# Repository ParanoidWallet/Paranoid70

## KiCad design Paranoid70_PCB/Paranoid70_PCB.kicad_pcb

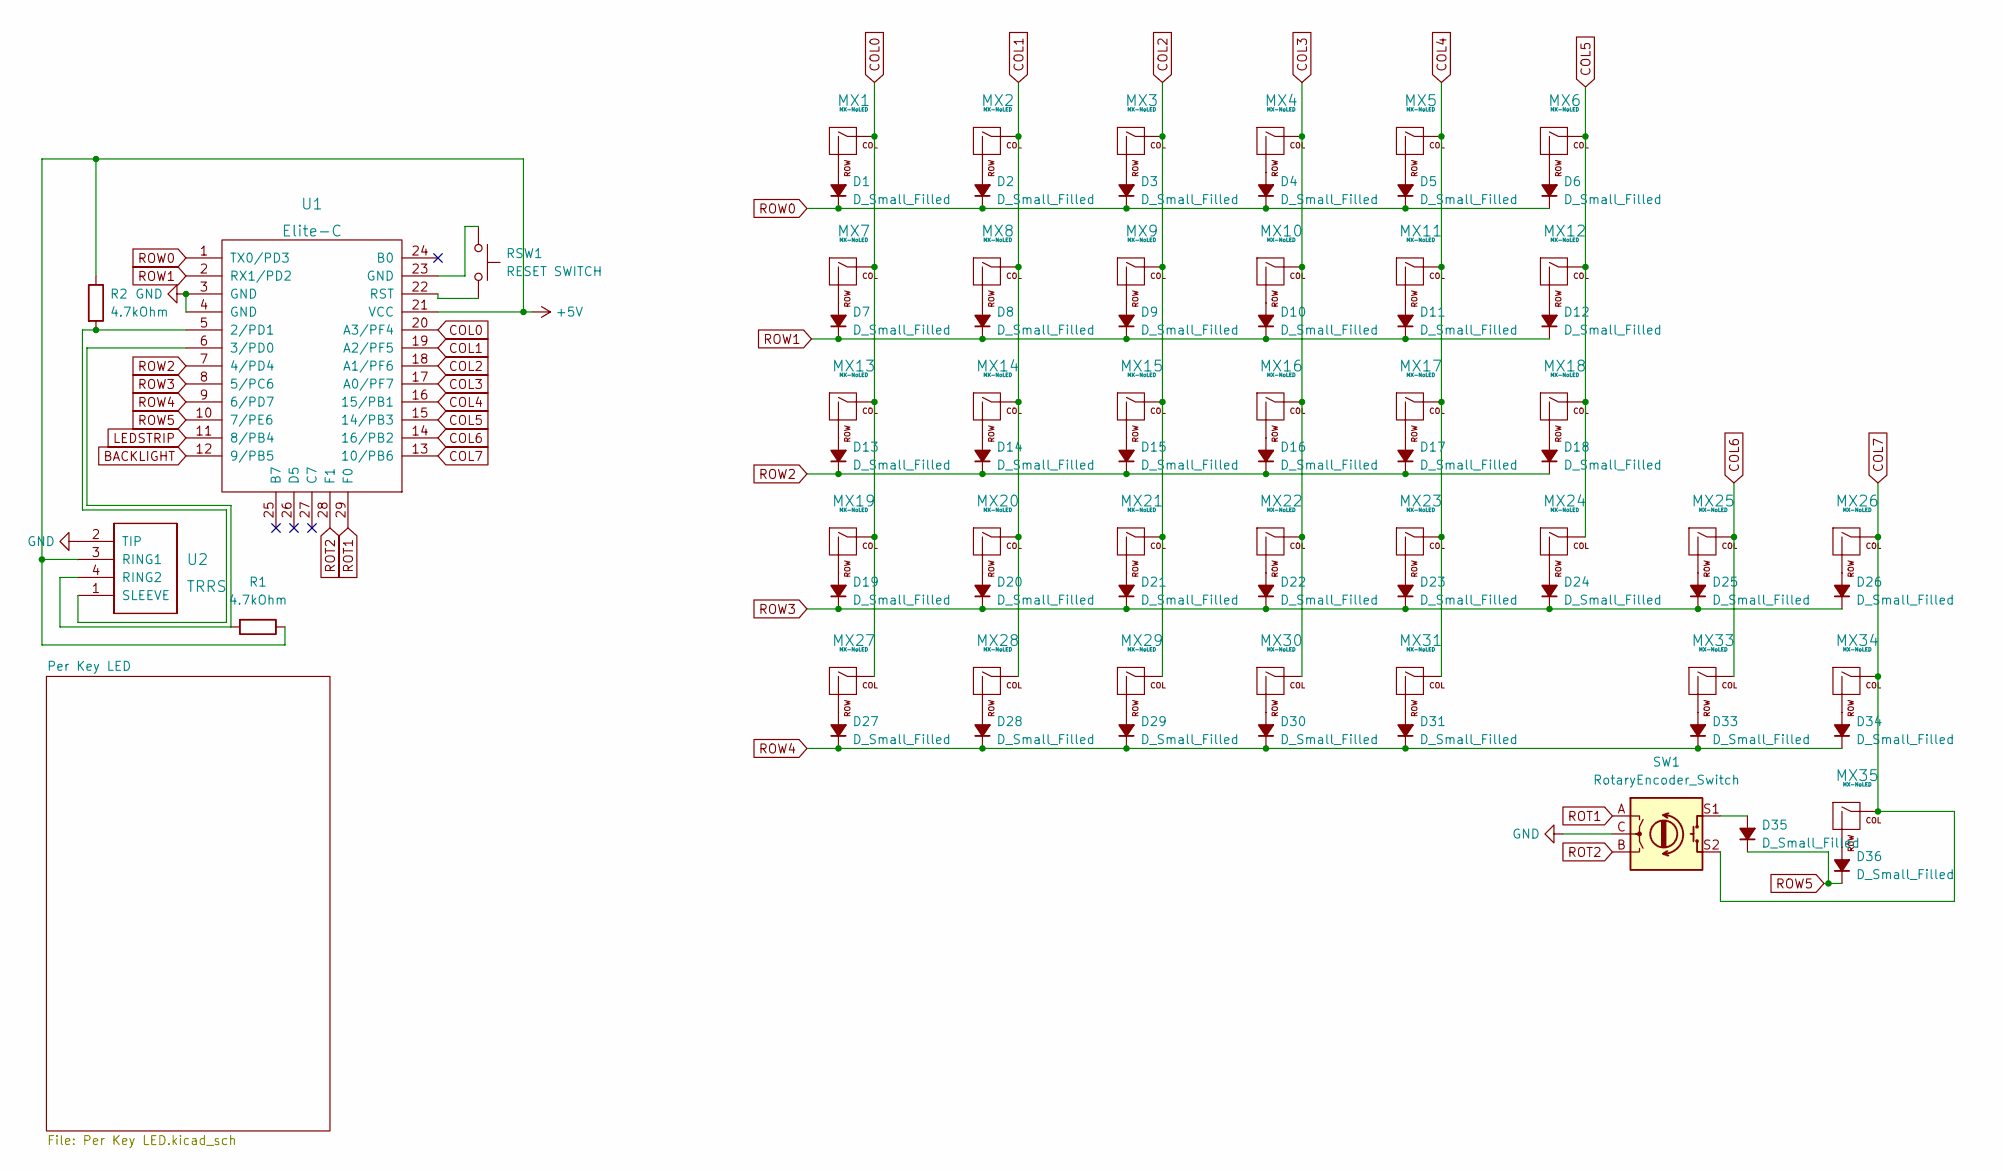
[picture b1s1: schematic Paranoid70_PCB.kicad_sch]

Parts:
D1, D2, D3, D4, D5, D6, D7, D8, D9, D10, D11, D12, D13, D14, D15, D16, D17, D18, D19, D20, D21, D22, D23, D24, D25, D26, D27, D28, D29, D30, D31, D33, D34, D35, D36: D_Small_Filled; Diode-hybrid-3pad
MX1, MX2, MX3, MX4, MX5, MX6, MX7, MX8, MX9, MX10, MX11, MX12, MX13, MX14, MX15, MX16, MX17, MX18, MX19, MX20, MX21, MX22, MX23, MX24, MX25, MX26, MX27, MX28, MX29, MX30, MX31, MX34, MX35: MX-NoLED; MX-Alps-Choc-1U-NoLED
MX33: MX-NoLED; MX-Alps-Choc-2U
R1, R2: 4.7kOhm; Resistor-Hybrid
RSW1: RESET SWITCH; SW_Tactile_SPST_Angled_MJTP1117
SW1: RotaryEncoder_Switch; RotaryEncoder_EC11
U1: Elite-C; Elite-C-castellated-29pin-holes
U2: TRRS; TRRS-PJ-320A

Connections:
+5V: R1.1, R2.1, U1.21 (VCC), U2.3 (RING1); also elsewhere on the board
BACKLIGHT: U1.12 (9/PB5); also elsewhere on the board
COL0: MX1.1 (COL), MX7.1 (COL), MX13.1 (COL), MX19.1 (COL), MX27.1 (COL), U1.20 (A3/PF4)
COL1: MX2.1 (COL), MX8.1 (COL), MX14.1 (COL), MX20.1 (COL), MX28.1 (COL), U1.19 (A2/PF5)
COL2: MX3.1 (COL), MX9.1 (COL), MX15.1 (COL), MX21.1 (COL), MX29.1 (COL), U1.18 (A1/PF6)
COL3: MX4.1 (COL), MX10.1 (COL), MX16.1 (COL), MX22.1 (COL), MX30.1 (COL), U1.17 (A0/PF7)
COL4: MX5.1 (COL), MX11.1 (COL), MX17.1 (COL), MX23.1 (COL), MX31.1 (COL), U1.16 (15/PB1)
COL5: MX6.1 (COL), MX12.1 (COL), MX18.1 (COL), MX24.1 (COL), U1.15 (14/PB3)
COL6: MX25.1 (COL), MX33.1 (COL), U1.14 (16/PB2)
COL7: MX26.1 (COL), MX34.1 (COL), MX35.1 (COL), SW1.S2, U1.13 (10/PB6)
GND: SW1.C, U1.3 (GND), U1.4 (GND), U2.2 (TIP); also elsewhere on the board
LEDSTRIP: U1.11 (8/PB4)
unnamed: D1.2 (A), MX1.2 (ROW)
unnamed: D2.2 (A), MX2.2 (ROW)
unnamed: D3.2 (A), MX3.2 (ROW)
unnamed: D4.2 (A), MX4.2 (ROW)
unnamed: D5.2 (A), MX5.2 (ROW)
unnamed: D6.2 (A), MX6.2 (ROW)
unnamed: D7.2 (A), MX7.2 (ROW)
unnamed: D8.2 (A), MX8.2 (ROW)
unnamed: D9.2 (A), MX9.2 (ROW)
unnamed: D10.2 (A), MX10.2 (ROW)
unnamed: D11.2 (A), MX11.2 (ROW)
unnamed: D12.2 (A), MX12.2 (ROW)
unnamed: D13.2 (A), MX13.2 (ROW)
unnamed: D14.2 (A), MX14.2 (ROW)
unnamed: D15.2 (A), MX15.2 (ROW)
unnamed: D16.2 (A), MX16.2 (ROW)
unnamed: D17.2 (A), MX17.2 (ROW)
unnamed: D18.2 (A), MX18.2 (ROW)
unnamed: D19.2 (A), MX19.2 (ROW)
unnamed: D20.2 (A), MX20.2 (ROW)
unnamed: D21.2 (A), MX21.2 (ROW)
unnamed: D22.2 (A), MX22.2 (ROW)
unnamed: D23.2 (A), MX23.2 (ROW)
unnamed: D24.2 (A), MX24.2 (ROW)
unnamed: D25.2 (A), MX25.2 (ROW)
unnamed: D26.2 (A), MX26.2 (ROW)
unnamed: D27.2 (A), MX27.2 (ROW)
unnamed: D28.2 (A), MX28.2 (ROW)
unnamed: D29.2 (A), MX29.2 (ROW)
unnamed: D30.2 (A), MX30.2 (ROW)
unnamed: D31.2 (A), MX31.2 (ROW)
unnamed: D33.2 (A), MX33.2 (ROW)
unnamed: D34.2 (A), MX34.2 (ROW)
unnamed: D35.2 (A), SW1.S1
unnamed: D36.2 (A), MX35.2 (ROW)
unnamed: R1.2, U1.6 (3/PD0), U2.4 (RING2)
unnamed: RSW1.1 (A), RSW1.2 (A), U1.23 (GND)
unnamed: RSW1.3 (B), RSW1.4 (B), U1.22 (RST)
unnamed: R2.2, U1.5 (2/PD1), U2.1 (SLEEVE)
ROT1: SW1.A, U1.29 (F0)
ROT2: SW1.B, U1.28 (F1)
ROW0: D1.1 (K), D2.1 (K), D3.1 (K), D4.1 (K), D5.1 (K), D6.1 (K), U1.1 (TX0/PD3)
ROW1: D7.1 (K), D8.1 (K), D9.1 (K), D10.1 (K), D11.1 (K), D12.1 (K), U1.2 (RX1/PD2)
ROW2: D13.1 (K), D14.1 (K), D15.1 (K), D16.1 (K), D17.1 (K), D18.1 (K), U1.7 (4/PD4)
ROW3: D19.1 (K), D20.1 (K), D21.1 (K), D22.1 (K), D23.1 (K), D24.1 (K), D25.1 (K), D26.1 (K), U1.8 (5/PC6)
ROW4: D27.1 (K), D28.1 (K), D29.1 (K), D30.1 (K), D31.1 (K), D33.1 (K), D34.1 (K), U1.9 (6/PD7)
ROW5: D35.1 (K), D36.1 (K), U1.10 (7/PE6)

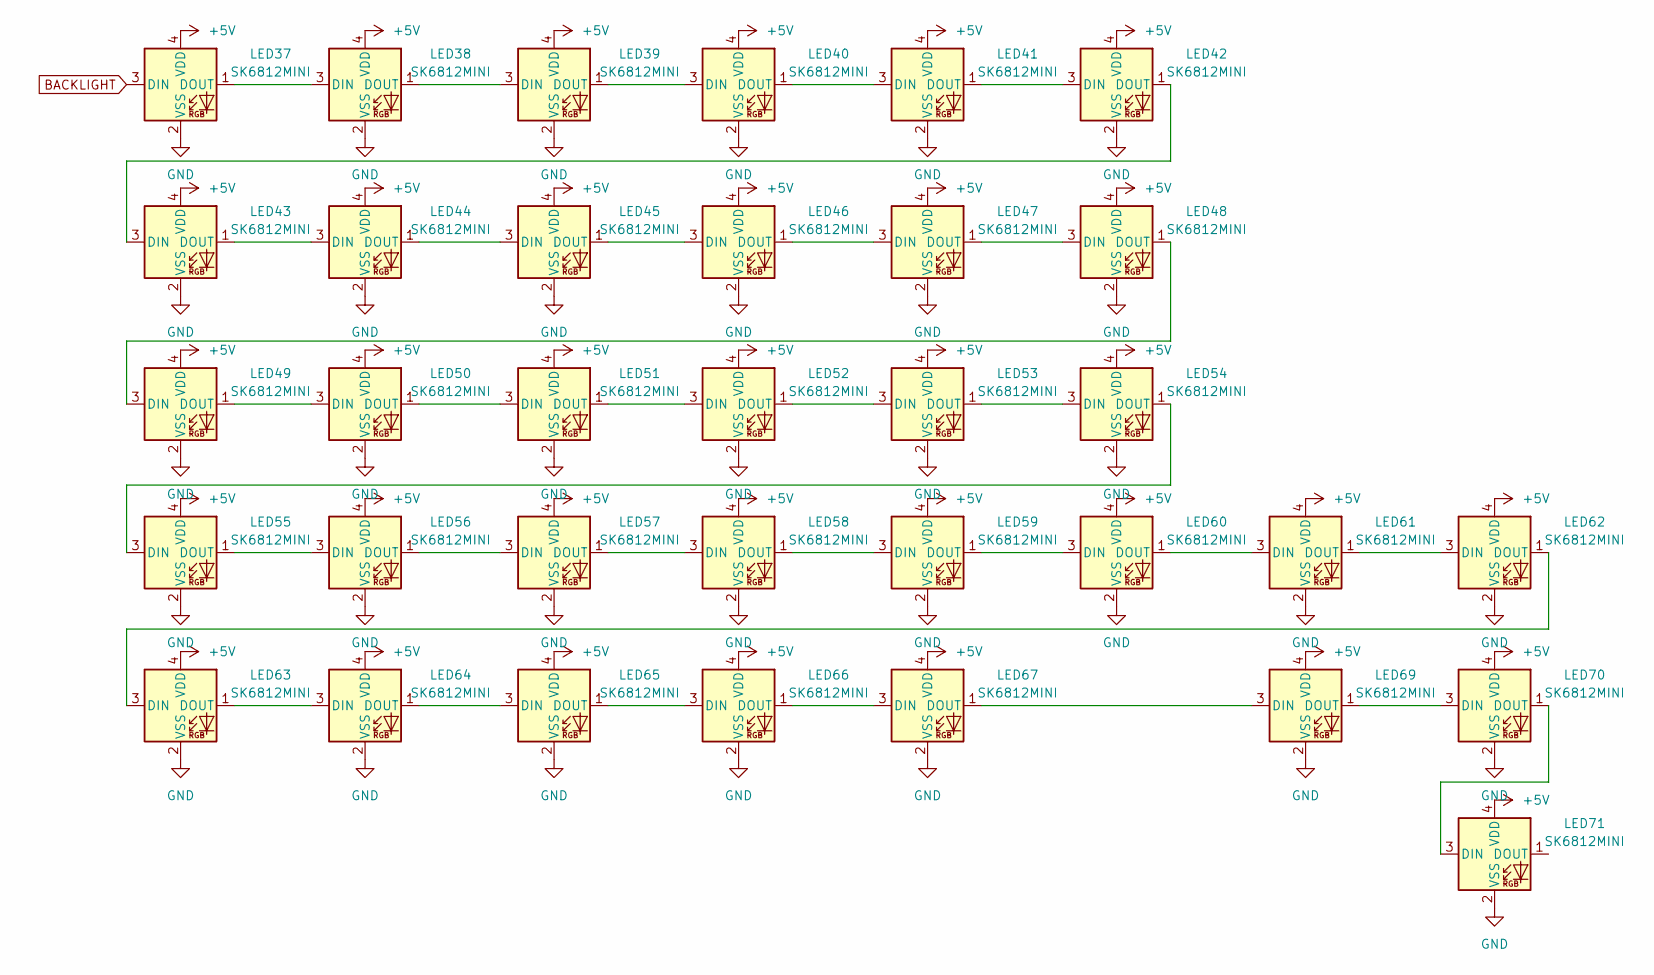
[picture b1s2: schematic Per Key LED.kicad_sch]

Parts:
LED37, LED38, LED39, LED40, LED41, LED42, LED43, LED44, LED45, LED46, LED47, LED48, LED49, LED50, LED51, LED52, LED53, LED54, LED55, LED56, LED57, LED58, LED59, LED60, LED61, LED62, LED63, LED64, LED65, LED66, LED67, LED69, LED70, LED71: SK6812MINI; SK6812-MINI-E

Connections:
+5V: LED37.4 (VDD), LED38.4 (VDD), LED39.4 (VDD), LED40.4 (VDD), LED41.4 (VDD), LED42.4 (VDD), LED43.4 (VDD), LED44.4 (VDD), LED45.4 (VDD), LED46.4 (VDD), LED47.4 (VDD), LED48.4 (VDD), LED49.4 (VDD), LED50.4 (VDD), LED51.4 (VDD), LED52.4 (VDD), LED53.4 (VDD), LED54.4 (VDD), LED55.4 (VDD), LED56.4 (VDD), LED57.4 (VDD), LED58.4 (VDD), LED59.4 (VDD), LED60.4 (VDD), LED61.4 (VDD), LED62.4 (VDD), LED63.4 (VDD), LED64.4 (VDD), LED65.4 (VDD), LED66.4 (VDD), LED67.4 (VDD), LED69.4 (VDD), LED70.4 (VDD), LED71.4 (VDD); also elsewhere on the board
BACKLIGHT: LED37.3 (DIN); also elsewhere on the board
GND: LED37.2 (VSS), LED38.2 (VSS), LED39.2 (VSS), LED40.2 (VSS), LED41.2 (VSS), LED42.2 (VSS), LED43.2 (VSS), LED44.2 (VSS), LED45.2 (VSS), LED46.2 (VSS), LED47.2 (VSS), LED48.2 (VSS), LED49.2 (VSS), LED50.2 (VSS), LED51.2 (VSS), LED52.2 (VSS), LED53.2 (VSS), LED54.2 (VSS), LED55.2 (VSS), LED56.2 (VSS), LED57.2 (VSS), LED58.2 (VSS), LED59.2 (VSS), LED60.2 (VSS), LED61.2 (VSS), LED62.2 (VSS), LED63.2 (VSS), LED64.2 (VSS), LED65.2 (VSS), LED66.2 (VSS), LED67.2 (VSS), LED69.2 (VSS), LED70.2 (VSS), LED71.2 (VSS); also elsewhere on the board
unnamed: LED37.1 (DOUT), LED38.3 (DIN)
unnamed: LED38.1 (DOUT), LED39.3 (DIN)
unnamed: LED39.1 (DOUT), LED40.3 (DIN)
unnamed: LED40.1 (DOUT), LED41.3 (DIN)
unnamed: LED41.1 (DOUT), LED42.3 (DIN)
unnamed: LED42.1 (DOUT), LED43.3 (DIN)
unnamed: LED43.1 (DOUT), LED44.3 (DIN)
unnamed: LED44.1 (DOUT), LED45.3 (DIN)
unnamed: LED45.1 (DOUT), LED46.3 (DIN)
unnamed: LED46.1 (DOUT), LED47.3 (DIN)
unnamed: LED47.1 (DOUT), LED48.3 (DIN)
unnamed: LED48.1 (DOUT), LED49.3 (DIN)
unnamed: LED49.1 (DOUT), LED50.3 (DIN)
unnamed: LED50.1 (DOUT), LED51.3 (DIN)
unnamed: LED51.1 (DOUT), LED52.3 (DIN)
unnamed: LED52.1 (DOUT), LED53.3 (DIN)
unnamed: LED53.1 (DOUT), LED54.3 (DIN)
unnamed: LED54.1 (DOUT), LED55.3 (DIN)
unnamed: LED55.1 (DOUT), LED56.3 (DIN)
unnamed: LED56.1 (DOUT), LED57.3 (DIN)
unnamed: LED57.1 (DOUT), LED58.3 (DIN)
unnamed: LED58.1 (DOUT), LED59.3 (DIN)
unnamed: LED59.1 (DOUT), LED60.3 (DIN)
unnamed: LED60.1 (DOUT), LED61.3 (DIN)
unnamed: LED61.1 (DOUT), LED62.3 (DIN)
unnamed: LED62.1 (DOUT), LED63.3 (DIN)
unnamed: LED63.1 (DOUT), LED64.3 (DIN)
unnamed: LED64.1 (DOUT), LED65.3 (DIN)
unnamed: LED65.1 (DOUT), LED66.3 (DIN)
unnamed: LED66.1 (DOUT), LED67.3 (DIN)
unnamed: LED67.1 (DOUT), LED69.3 (DIN)
unnamed: LED69.1 (DOUT), LED70.3 (DIN)
unnamed: LED70.1 (DOUT), LED71.3 (DIN)

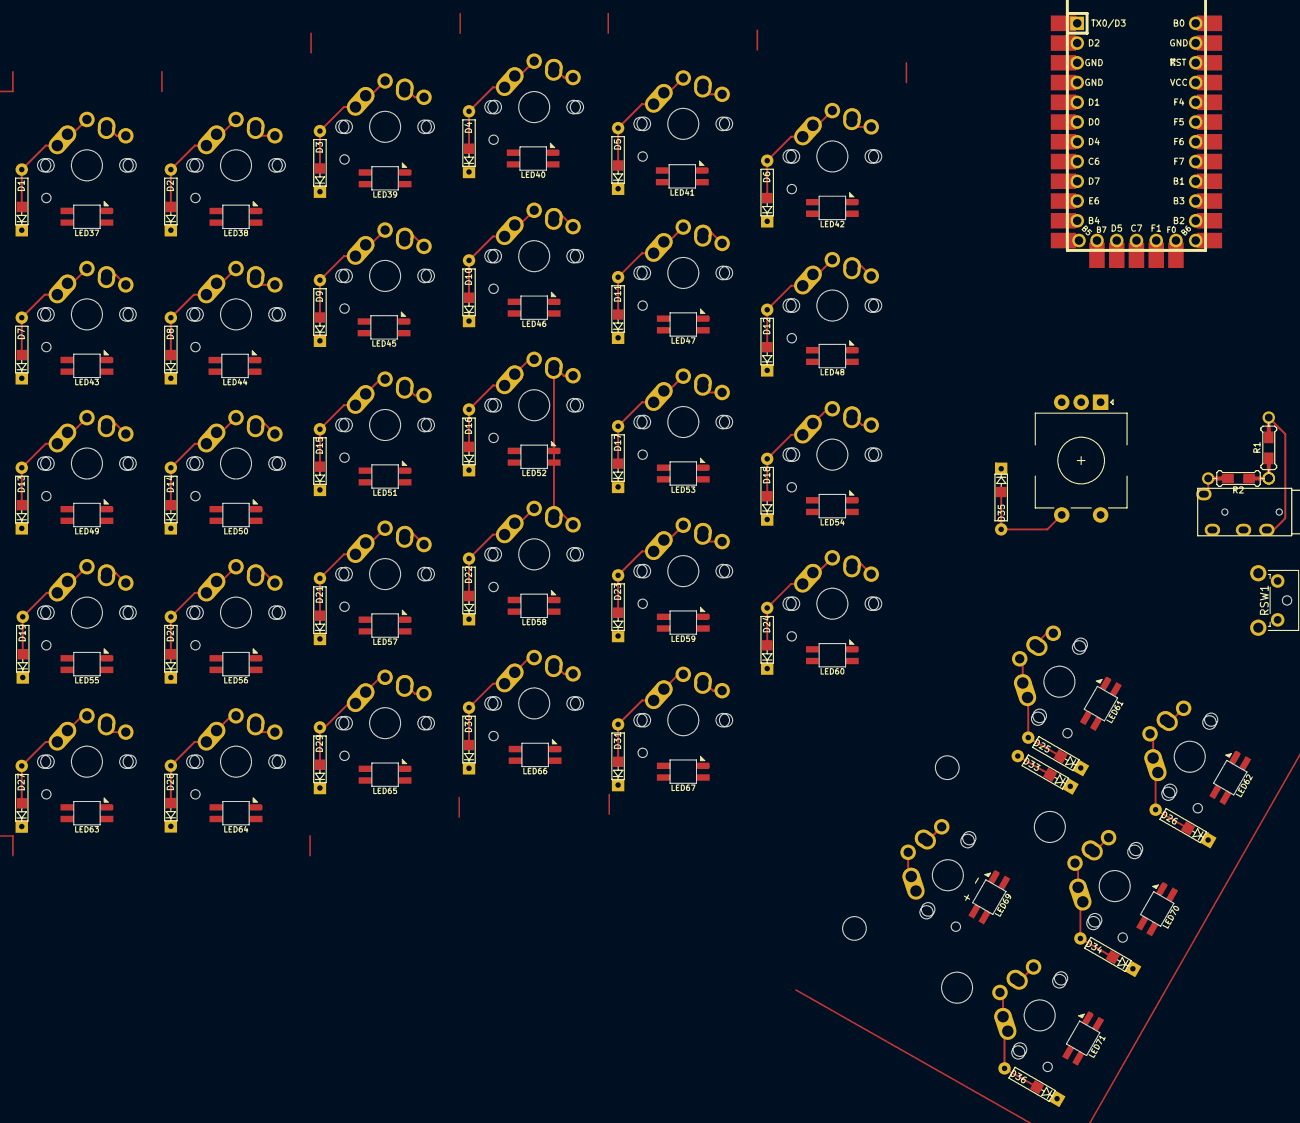
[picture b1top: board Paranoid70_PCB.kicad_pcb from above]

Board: 2 copper layers, 109 parts (0 on the bottom side), 90 nets.

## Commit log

2023-02-17 Base files and Schema added
    Everything has been updated and added to match my progress so far
2023-02-19 Schema Finish and first go at the PCB
2023-02-20 PCB 90% complete
